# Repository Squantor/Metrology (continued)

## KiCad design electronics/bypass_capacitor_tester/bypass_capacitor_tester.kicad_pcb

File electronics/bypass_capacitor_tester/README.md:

# Bypass capacitor tester
This project is based on the test jig by [Jim Williams in Linear application note 72](https://www.analog.com/media/en/technical-documentation/application-notes/an72f.pdf), see figure 42 for the schematic. This project is a practical implementation of this schematic.
## TODO's
Still some things need to be done:
* schematic entry (WIP)
* PCB layout (TODO)
* Review with one night in between (TODO)
* Produce at [OSHPARK](https://oshpark.com/) (TODO)
* Assemble (TODO)
* Test & characterise (TODO)
* update Readme.md with pictures and BOM (TODO)
## BOM
## Pictures

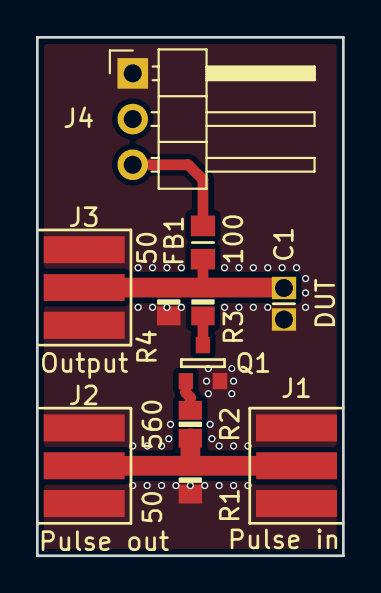
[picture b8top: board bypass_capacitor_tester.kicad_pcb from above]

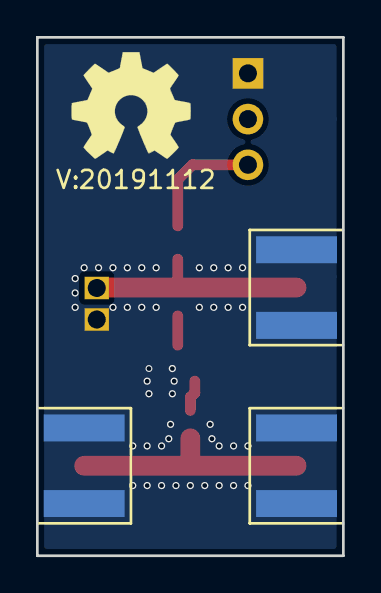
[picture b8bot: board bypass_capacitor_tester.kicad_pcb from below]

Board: 2 copper layers, 17.0 x 28.8 mm, 13 parts (2 on the bottom side), 6 nets.

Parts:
C1: DUT; C_TH+0805+0603+0402
FB1: Ferrite_Bead; C_0805+0603
J1: Pulse in; SMA_edge_6mm2
J2: Pulse out; SMA_edge_6mm2
J3: Output; SMA_edge_6mm2
J4: Conn_01x02; PinHeader_1x03_P2.54mm_Horizontal
N1: OHWLOGO; OSHW-Symbol_6.7x6mm_SilkScreen
N2: 20191112; Label_version
Q1: MMBT2369AL; SOT23-3
R1, R4: 50; R_0805+0603
R2: 560; R_0805+0603
R3: 100; R_0805+0603

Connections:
/A_WAVEFORM: J1.1, J2.1, R1.1, R2.2
/B_WAVEFORM: C1.1, FB1.2, J3.1, R3.1, R4.1
GND: C1.2, J1.2, J2.2, J3.2, J4.1, Q1.2, R1.2, R4.2
unnamed: Q1.1, R2.1
unnamed: Q1.3, R3.2
VDD: FB1.1, J4.3

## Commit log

2015-03-19 * Added Geller SVR board outline clone with plated through holes. This is to make future references compatible with this form factor.
2015-03-19 * Started with the LTC6655 reference board, same form factor as the geller voltage reference
2015-03-19 * start of the LM399 board, copied the Geller board dimensions
2015-03-19 * added start of the lm399 reference
2015-03-23 * Additional work with LM399
2015-03-26 * finished LM399 breakout with a optional filter stage
2015-03-26 * Final touchups on LM399 breakout board, ready to order!
2015-04-09 * added hp34401a control application
2015-04-09 * added first modules
2015-04-16 * fixed mistakes with the lm399 board
2016-02-10 * added fluke845 references board project
2016-02-10 * layed out fluke845 reference board
2016-02-10 * small fixes on the PCB
2016-02-10 * added PB1 powersupply project * added LT1021 project (preparation for LT1236LS8 tester)
2016-02-20 * started on the PB1 powersupply
2016-02-21 * started with LTC2400 test board, but... its better to just begin with a PB1 sized board * started with PB1 board with LTC2400 etc
2016-02-21 * updated PB1 board, need a lot more lessons learned with it, so lets leave it for now * updated LTC2400 test board, going to focus on that first
2016-02-22 * added a bunch of reference modules, starting with LTC6655's
2016-02-22 * added ADC modules, first up the MCP3551 ADC
2016-02-23 * finished ltc6655 reference board
2016-02-23 * small modifications on ltc2400_adc_module
2016-02-23 * removed old unused project * switched to module outline layout, this way i am sure the boards will remain the same
2016-02-23 * updated and almost finished MCP3551 ADC module
2016-02-24 * updated board format * made the LTC6655 reference module more compact, hopefully better * small modifications to the MCP355X ADC module
2016-03-02 * modified boards and processed for production
2016-03-07 * populating initial project
2016-03-07 * cleaned up files from old project
2016-03-13 * Made functional MCP355X driver thingy
2016-03-13 * project file update
2016-03-14 * readout of MCP3550, some strange things are happening... Need electrical tests
2016-03-18 * some extra statistics added * fixed calculation from LSB to volt, loss of precision
2016-03-24 * small updates to voltmeter, adapted to optoisolation
2016-12-10 * moved all the PCB projects made in eagle to their own dir
2016-12-10 * created a MCP355X breakout module
2016-12-10 * added LTC6655 breakout module
2016-12-10 * created module for REF50XX series references
2016-12-10 * started with the MCP355X module fillout
2016-12-10 * finished routing MCP355X PCB
2016-12-10 * added OHSW logo and version
2016-12-10 * small mods and optimizations
2016-12-10 * again some small modifications
2016-12-10 * added LTC2400 module
2016-12-11 * project updates
2016-12-13 * changed input filter caps from 0603 to 0805
2016-12-19 * small mods
2016-12-20 * added REF schematic stuff
2016-12-21 * placed components on PCB and started positioning
2016-12-21 * more PCB layout stuff
2016-12-22 * added terminator module
2016-12-22 * added attenuator module
2016-12-22 * added partially routed pcb for the terminator
2016-12-27 * Some more layouting of the REF50XX module
2017-01-07 * changed bad footprints for the WIMA MKS-02 1uF caps
2017-01-07 * changes a mistake on layouting on wrong grid
2017-01-07 * added git ignore
2017-01-07 * updated the LTC6655 reference board
2017-01-07 * more ignores
2017-01-07 * some small modifications
2017-01-07 * redid partially REF5040 reference board
2017-11-10 * added a few dirs for the babims project * touched a few README.md's
2017-11-10 * added kicad projects
2017-11-10 * different naming scheme
2017-11-10 * added 3 babims expansion card * added 1 babims motherboard
2017-11-10 * added some explanation of the BABIMS project
2017-11-10 * project updates for prototyping card
2017-11-11 * started on the babims prototyping board
2017-11-13 * added hp 15 pin card extender project
2017-11-13 * modified .gitignore * added all the missing -cache.lib files * updated the hp card extender 15 pins
2017-11-27 * added new 96 pin backplane for babims
2017-11-27 * first definition of the connection nets
2018-12-15 reorganisation of the metrology collection library
2018-12-15 add private pcb component library
2018-12-15 added Readme with checkout instructions
2018-12-15 updated root readme with additional instructions
2018-12-15 added initial project for the endpoint unit of the flatcable jig system
2018-12-15 updated schematic with a few parts
2018-12-15 updated library
2018-12-15 started layout, still need to add the endpad connections
2018-12-16 single quotes are not backticks ;-)
2018-12-16 updated library with newer coaxial connections
2018-12-16 layout completed, now silk screen
2018-12-16 updated silkscreen position
2018-12-16 added box image
2018-12-16 updated versionnumber, adjusted cutout line thickness to 0.1mm
2018-12-17 added cache library
2018-12-17 added jumperable grounds
2019-01-21 updated pcb library
2019-01-21 updated versionnumbers, no real changes actually
2019-08-09 moved extender card project
2019-08-09 updated submodule
2019-08-09 added wheatstone bridge+hamon divider project
2019-08-09 updated gitignore
2019-08-09 added mounting holes and case net
2019-08-09 added initial Wheatstone bridge and Hamon divider
2019-08-10 added LT1021 reference project start, already added reference and trim schematic
2019-11-05 updated to newer PCB library
2019-11-05 added bypass capacitor tester project
2019-11-05 completed schematic
2019-11-05 fixed all ERC errors
2019-11-05 started layout
2019-11-10 newer PCB library
2019-11-10 removed defunct footprint library
2019-11-10 changed coaxial connectors to SMA edge connectors
2019-11-10 further placement
2019-11-12 changed power connector to something I use often
2019-11-12 changed dut footprint, placement completed
2019-11-12 silk placement completed
2019-11-12 updated versionnumber
2022-09-23 moving around files
2022-09-23 harmonized with generic project library
2022-09-25 started with dslogic logic analyzer breakout board
2022-09-25 completed schematic, board layout and updated readme
2022-09-26 added some coplanar waveguides
2022-09-30 start with 4 pin logic analyzer probe
2022-09-30 edge footprints for probes
2022-09-30 added labels
2022-09-30 made unplaceable labels invisible
2022-09-30 updated pinout
2022-10-03 copied over 4 channel logic probe to 8
2022-10-03 updated to 8 channels
2022-10-03 WIP routing and placing
2022-10-04 WIP 8 channel dslogic probe
2022-10-07 fixing connector DRC issues
2022-10-07 fixed DRC issues with connectors
2022-10-07 added breakout for broadcom SiPM
2022-10-07 WIP schematic entry
2022-10-07 Started initial layout for breakout
2022-10-09 updated versionnumber and reviewed
2022-10-09 reviewd 4 bit logic probe circuit
2022-10-09 reviewed PCB and updated versionnumber
2023-04-14 minor changes
2023-04-14 started with notch filter project
2023-04-15 further layout and placing
2023-04-15 added filter and attenuator to schematic and placed components
2023-04-19 changed resistor networks to be more flexible, placed some components
2023-04-19 added compensation capacitor, placed and routed filter
2023-04-20 footprint changes, changed power rails, silk placed, added labels, increased size of labels
2023-04-21 added 1M input resistor
2023-04-21 started with oscillator prototyping board
2023-04-21 layout completed on prototype oscillator prototype
2023-04-23 updated resistor values and some minor routing updates
2023-04-28 fixed errors with proto oscillator
2023-04-28 added additional adjust resistor and updated values
2023-04-28 started with PCB layout of single dual opamp with standard gain control
2023-04-28 placing and routing in progress, changed some ordering of resistors
2023-04-28 updated parts
2023-04-28 placing and routing further
2023-04-30 updated some shielded components, changing routing of some nets keeping the ground plane as much contigious as possible
2023-04-30 place and route and silk placement completed
2023-05-01 small modification made to select output point
2023-05-01 started variant 2 of high purity oscillator
2023-05-01 added oscillator variant with dual single opamp
2023-05-01 completed place and routing
2023-05-01 updated footprints
2023-05-07 ERC/DRC passes, small ergonomic changes
2023-05-07 reviewed
2023-05-07 review completed
2023-05-07 small changes in output pin
2023-05-30 updated notch filter
2023-05-31 fixed aisler warnings/errors
2023-07-01 conversion to kicad 7
2023-07-17 removed labels and minor optimisations
2023-07-17 copied notch filter to a SMT version
2024-03-29 started with linear technology style wien bridge oscillator
2024-04-03 added vactrol housing files
2024-05-03 added passive filter project
2024-05-03 updated with kicad 7 ignores
2024-05-03 completed passive filter
